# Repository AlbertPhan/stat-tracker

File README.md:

### For more pictures and info see:
www.pegasusprototyping.ca/stattracker

# Stat Tracker
The ***Stat Tracker*** is a portable battery powered device that keeps track of ***health, energy, and dashes*** for the Hyper Light Drifter Table Top Role Playing Game. Although it was designed with Hyper Light Drifter in mind, it could be used in other table top games like Dungeons and Dragons. 

Features:

 - Tracks 40 points of Health and Energy and 10 points in Dashes
 - Bright RGB leds for each icon
 - Custom art in Hyper Light Drifter theme
 - Unique Slim PCB sandwich construction with special icons for LED diffusion
 - 6 physical pcb buttons to add/subtract points
 - 2 touch buttons for brightness control
 - Customizable colour palettes including colourblind modes
 - USB micro for charging
 - 8 hours of battery life on default brightness and battery charge indicator icon
 - Stats are saved on power off.

 # Code

 The stat tracker uses a very cheap 50 cent chinese mcu called the CH552. The tool chain setup is explained in https://github.com/Blinkinlabs/ch554_sdcc.

 The stat tracker code is contained in the examples folder "examples/stat_tracker"

 Some c files were created/modified to help use the ch552 such as:
 - button.c     usage of buttons and their states
 - touch.c      touch button usage
 - timer.c      set up timers for millis()

 # Eagle Source files

Eagle Source files are included. (Eagle Version 9.6.1 was used). See README in Eagle files for bom/board information.

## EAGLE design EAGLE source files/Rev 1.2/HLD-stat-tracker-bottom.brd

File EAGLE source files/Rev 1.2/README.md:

# Boards
For a full PCB sandwich you will need:
1 Top
1 Middle
1 Bottom
3 Spacers
1 Box Art
Send additional info the board house such as led pinout png and note that the pads on the bottom of the bottom board are supposed to have solder mask (no exposed pad) over them.

# BOM
Bom is located in the GERBER bottom assembly "\Rev 1.2\Gerber\HLD-stat-tracker-bottom_2020-12-04\CAMOutputs\Assembly\HLD-stat-tracker-bottom-BOM.csv"
LEDS used are a 2020 type with SK6812 like pinout (not the same as ws2812-2020). Please triple check the pinouts if you are using something other than leds in the BOM.

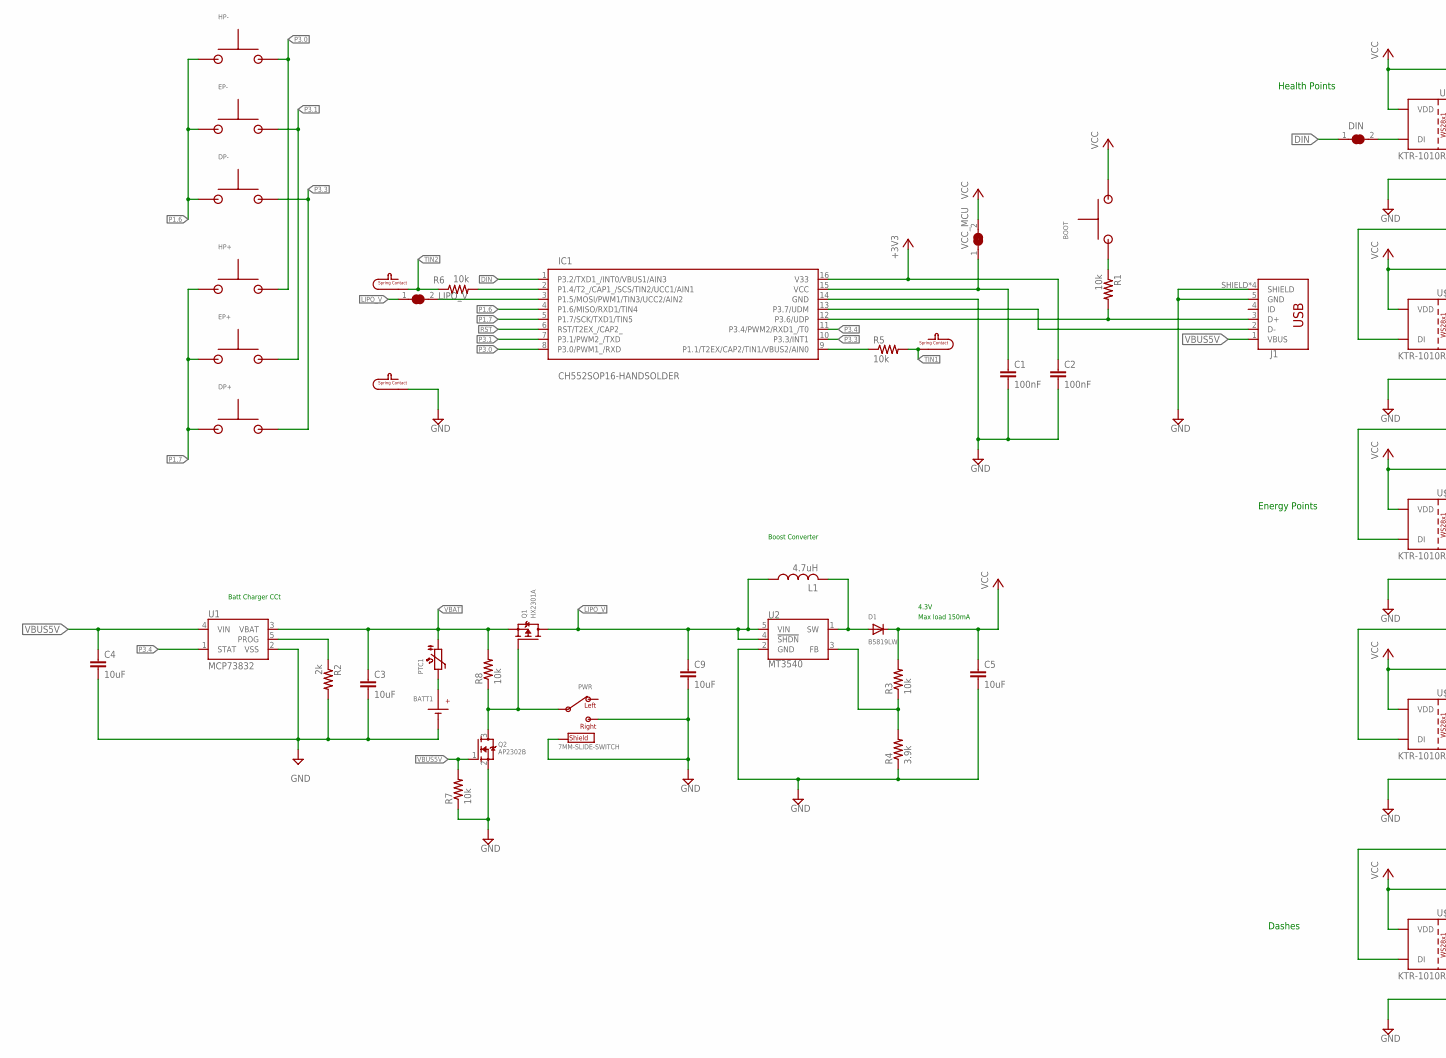
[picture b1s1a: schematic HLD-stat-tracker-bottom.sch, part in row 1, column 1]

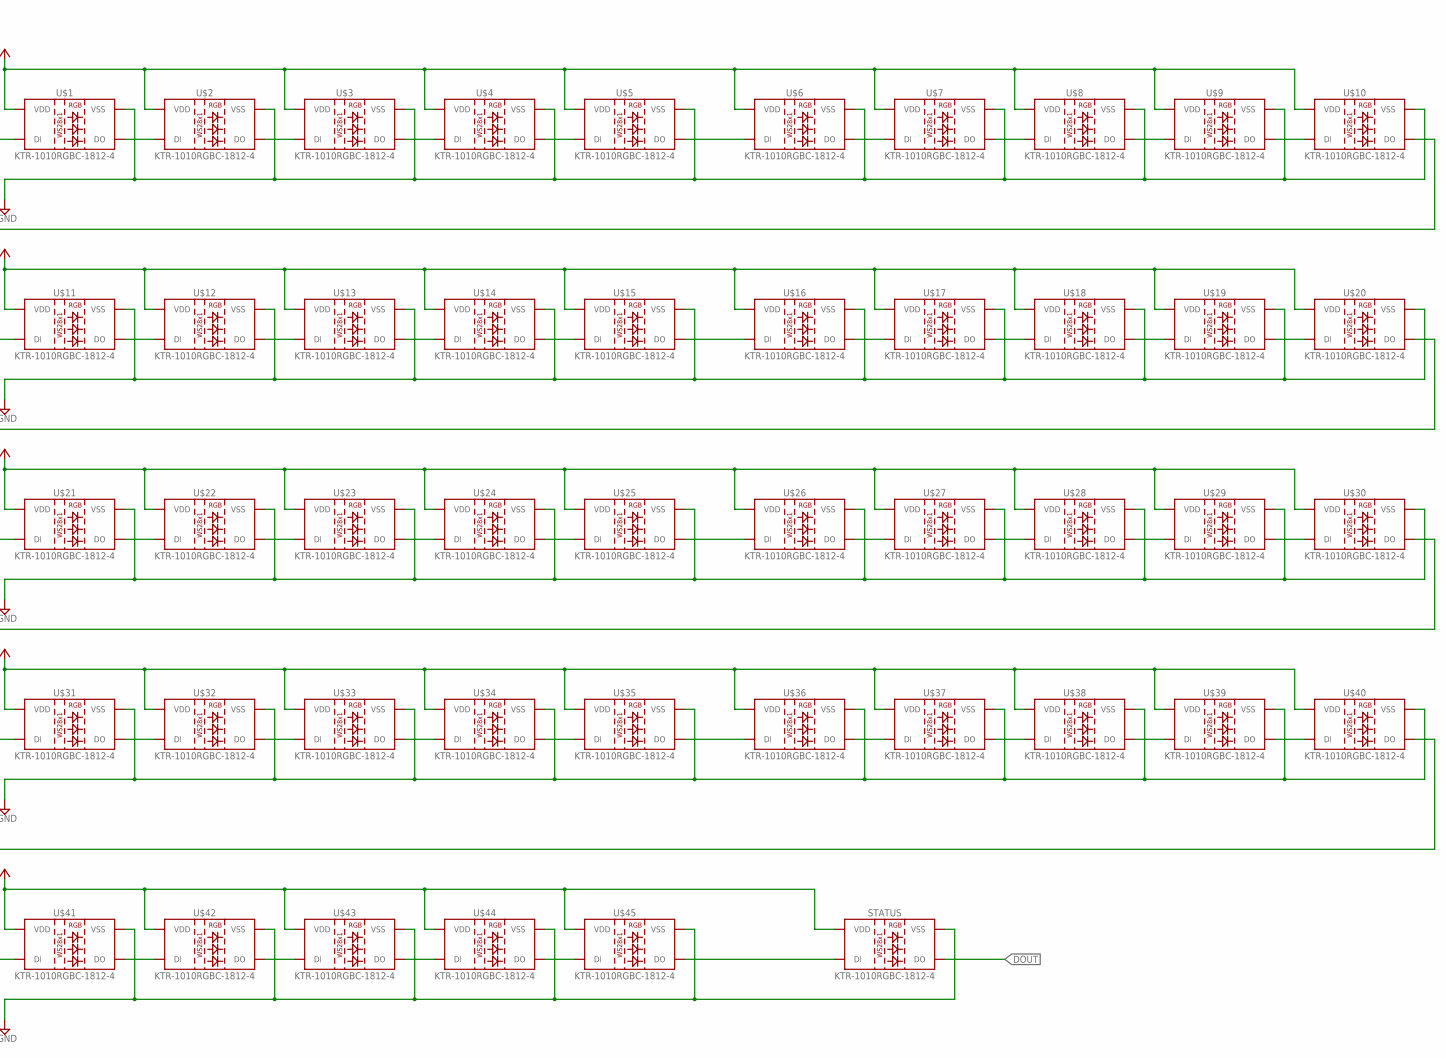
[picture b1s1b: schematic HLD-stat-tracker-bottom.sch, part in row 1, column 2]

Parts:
BATT1: BATT+; BATT+PAD; PARTNO ?
BATT1-: BATT-; BATT-PAD; PARTNO ?
BOOT: TACTSW; 3MM-TACT
C1, C2: 100nF; C0805K; PARTNO ?
C3, C4, C5, C9: 10uF; C0805K; PARTNO ?
D1: B5819LW; SOD-123; PARTNO B5819LW
DIN: SOLDERJUMPER-NC; SOLDERJUMPER_CLOSEDWIRE_SMALL
DP+: TACTSW; 3MM-TACT
DP-: TACTSW; 3MM-TACT
EP+: TACTSW; 3MM-TACT
EP-: TACTSW; 3MM-TACT
GND: SPRING-CONTACT; 818000905-SPRING-CONTACT
HP+: TACTSW; 3MM-TACT
HP-: TACTSW; 3MM-TACT; PARTNO TS3315A
IC1: CH552SOP16-HANDSOLDER; SOP16-HANDSOLDER
J1: USB_MICRO-BSINK-PLATE; USB-B-MICRO-SMD-SINK-PLATE
L1: 4.7uH; BEADC2012X105N
LIPO_V: SOLDERJUMPER-NC; SOLDERJUMPER_CLOSEDWIRE_SMALL
PTC1: PTC0805; WCAP-CSGP_0805_H1.25_R
PWR: 7MM-SLIDE-SWITCH; 7MM-SMD-SLIDE-SWITCH
Q1: HX2301A; SOT23-R
Q2: AP2302B; SOT23-R
R1, R3, R5, R6, R7, R8: 10k; R0805S; PARTNO ?
R2: 2k; R0805S; PARTNO ?
R4: 3.9k; R0805S; PARTNO ?
STATUS: KTR-1010RGBC-1812-4; SK6812-2020
TIN1, TIN2: SPRING-CONTACT; 818000905-SPRING-CONTACT
U1: MCP73832; SOT23-5; PARTNO MCP73832
U2: MT3540; SOT23-5; PARTNO MT3540
U$1, U$2, U$3, U$4, U$5, U$6, U$7, U$8, U$9, U$10, U$11, U$12, U$13, U$14, U$15, U$16, U$17, U$18, U$19, U$20, U$21, U$22, U$23, U$24, U$25, U$26, U$27, U$28, U$29, U$30, U$31, U$32, U$33, U$34, U$35, U$36, U$37, U$38, U$39, U$40, U$41, U$42, U$43, U$44, U$45: KTR-1010RGBC-1812-4; SK6812-2020
VCC_MCU: SOLDERJUMPER-NC; SOLDERJUMPER_CLOSEDWIRE_SMALL

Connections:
+3V3: C2.1, IC1.16 (V33)
DIN: DIN.1, IC1.1 (P3.2/TXD1_/INT0/VBUS1/AIN3)
DIN_: DIN.2, U$1.DIN (DI)
DOUT: STATUS.DOUT (DO)
FB: R3.1, R4.2, U2.3 (FB)
GND: BATT1-.P$1, C1.2, C2.2, C3.2, C4.2, C5.2, C9.2, GND.P$1, IC1.14 (GND), J1.5 (GND), J1.SHIELD, J1.SHIELD2 (SHIELD), J1.SHIELD3 (SHIELD), J1.SHIELD4 (SHIELD), PWR.3, PWR.GND@1 (SHIELD), PWR.GND@2 (SHIELD), PWR.GND@3 (SHIELD), PWR.GND@4 (SHIELD), Q2.2 (S), R2.2, R4.1, R7.1, STATUS.VSS, U1.2 (VSS), U2.2 (GND), U$1.VSS, U$2.VSS, U$3.VSS, U$4.VSS, U$5.VSS, U$6.VSS, U$7.VSS, U$8.VSS, U$9.VSS, U$10.VSS, U$11.VSS, U$12.VSS, U$13.VSS, U$14.VSS, U$15.VSS, U$16.VSS, U$17.VSS, U$18.VSS, U$19.VSS, U$20.VSS, U$21.VSS, U$22.VSS, U$23.VSS, U$24.VSS, U$25.VSS, U$26.VSS, U$27.VSS, U$28.VSS, U$29.VSS, U$30.VSS, U$31.VSS, U$32.VSS, U$33.VSS, U$34.VSS, U$35.VSS, U$36.VSS, U$37.VSS, U$38.VSS, U$39.VSS, U$40.VSS, U$41.VSS, U$42.VSS, U$43.VSS, U$44.VSS, U$45.VSS
LIPO_V: C9.1, L1.1, LIPO_V.1, Q1.3 (D), U2.4 (!SHDN!), U2.5 (VIN)
LIPO_V_MCU: IC1.3 (P1.5/MOSI/PWM1/TIN3/UCC2/AIN2), LIPO_V.2
unnamed: IC1.9 (P1.1/T2EX/CAP2/TIN1/VBUS2/AIN0), R5.1
unnamed: BATT1.P$1, PTC1.2
unnamed: IC1.2 (P1.4/T2_/CAP1_/SCS/TIN2/UCC1/AIN1), R6.2
unnamed: PWR.2, Q1.1 (G), Q2.3 (D), R8.1
unnamed: U$1.DOUT (DO), U$2.DIN (DI)
unnamed: U$6.DOUT (DO), U$7.DIN (DI)
unnamed: R2.1, U1.5 (PROG)
unnamed: U$20.DOUT (DO), U$21.DIN (DI)
unnamed: U$11.DOUT (DO), U$12.DIN (DI)
unnamed: U$16.DOUT (DO), U$17.DIN (DI)
unnamed: U$12.DOUT (DO), U$13.DIN (DI)
unnamed: U$13.DOUT (DO), U$14.DIN (DI)
unnamed: U$14.DOUT (DO), U$15.DIN (DI)
unnamed: U$15.DOUT (DO), U$16.DIN (DI)
unnamed: U$2.DOUT (DO), U$3.DIN (DI)
unnamed: U$3.DOUT (DO), U$4.DIN (DI)
unnamed: U$4.DOUT (DO), U$5.DIN (DI)
unnamed: U$5.DOUT (DO), U$6.DIN (DI)
unnamed: U$7.DOUT (DO), U$8.DIN (DI)
unnamed: U$8.DOUT (DO), U$9.DIN (DI)
unnamed: U$9.DOUT (DO), U$10.DIN (DI)
unnamed: U$17.DOUT (DO), U$18.DIN (DI)
unnamed: U$18.DOUT (DO), U$19.DIN (DI)
unnamed: U$19.DOUT (DO), U$20.DIN (DI)
unnamed: U$10.DOUT (DO), U$11.DIN (DI)
unnamed: U$21.DOUT (DO), U$22.DIN (DI)
unnamed: U$26.DOUT (DO), U$27.DIN (DI)
unnamed: U$22.DOUT (DO), U$23.DIN (DI)
unnamed: U$23.DOUT (DO), U$24.DIN (DI)
unnamed: U$24.DOUT (DO), U$25.DIN (DI)
unnamed: U$25.DOUT (DO), U$26.DIN (DI)
unnamed: U$27.DOUT (DO), U$28.DIN (DI)
unnamed: U$28.DOUT (DO), U$29.DIN (DI)
unnamed: U$29.DOUT (DO), U$30.DIN (DI)
unnamed: U$31.DOUT (DO), U$32.DIN (DI)
unnamed: U$36.DOUT (DO), U$37.DIN (DI)
unnamed: U$32.DOUT (DO), U$33.DIN (DI)
unnamed: U$33.DOUT (DO), U$34.DIN (DI)
unnamed: U$34.DOUT (DO), U$35.DIN (DI)
unnamed: U$35.DOUT (DO), U$36.DIN (DI)
unnamed: U$37.DOUT (DO), U$38.DIN (DI)
unnamed: U$38.DOUT (DO), U$39.DIN (DI)
unnamed: U$39.DOUT (DO), U$40.DIN (DI)
unnamed: U$30.DOUT (DO), U$31.DIN (DI)
unnamed: U$41.DOUT (DO), U$42.DIN (DI)
unnamed: U$42.DOUT (DO), U$43.DIN (DI)
unnamed: U$43.DOUT (DO), U$44.DIN (DI)
unnamed: U$44.DOUT (DO), U$45.DIN (DI)
unnamed: STATUS.DIN (DI), U$45.DOUT (DO)
unnamed: U$40.DOUT (DO), U$41.DIN (DI)
unnamed: BOOT.1, BOOT.2, R1.1
P1.6: DP-.1, DP-.2, EP-.1, EP-.2, HP-.1, HP-.2, IC1.4 (P1.6/MISO/RXD1/TIN4)
P1.7: DP+.1, DP+.2, EP+.1, EP+.2, HP+.1, HP+.2, IC1.5 (P1.7/SCK/TXD1/TIN5)
P3.0: HP+.3, HP+.4, HP-.3, HP-.4, IC1.8 (P3.0/PWM1_/RXD)
P3.1: EP+.3, EP+.4, EP-.3, EP-.4, IC1.7 (P3.1/PWM2_/TXD)
P3.3: DP+.3, DP+.4, DP-.3, DP-.4, IC1.10 (P3.3/INT1)
P3.4: IC1.11 (P3.4/PWM2/RXD1_/T0), U1.1 (STAT)
RST: IC1.6 (RST/T2EX_/CAP2_)
SW: D1.A, L1.2, U2.1 (SW)
TIN1: R5.2, TIN1.P$1
TIN2: R6.1, TIN2.P$1
UDM: IC1.13 (P3.7/UDM), J1.2 (D-)
UDP: IC1.12 (P3.6/UDP), J1.3 (D+), R1.2
VBAT: C3.1, PTC1.1, Q1.2 (S), R8.2, U1.3 (VBAT)
VBUS5V: C4.1, J1.1 (VBUS), Q2.1 (G), R7.2, U1.4 (VIN)
VCC: BOOT.3, BOOT.4, C5.1, D1.C, R3.2, STATUS.VDD, U$1.VDD, U$2.VDD, U$3.VDD, U$4.VDD, U$5.VDD, U$6.VDD, U$7.VDD, U$8.VDD, U$9.VDD, U$10.VDD, U$11.VDD, U$12.VDD, U$13.VDD, U$14.VDD, U$15.VDD, U$16.VDD, U$17.VDD, U$18.VDD, U$19.VDD, U$20.VDD, U$21.VDD, U$22.VDD, U$23.VDD, U$24.VDD, U$25.VDD, U$26.VDD, U$27.VDD, U$28.VDD, U$29.VDD, U$30.VDD, U$31.VDD, U$32.VDD, U$33.VDD, U$34.VDD, U$35.VDD, U$36.VDD, U$37.VDD, U$38.VDD, U$39.VDD, U$40.VDD, U$41.VDD, U$42.VDD, U$43.VDD, U$44.VDD, U$45.VDD, VCC_MCU.2
VCC_MCU: C1.1, IC1.15 (VCC), VCC_MCU.1

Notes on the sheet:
Health Points
Energy Points
Dashes
Batt Charger CCt
Boost Converter
Max load 150mA
4.3V

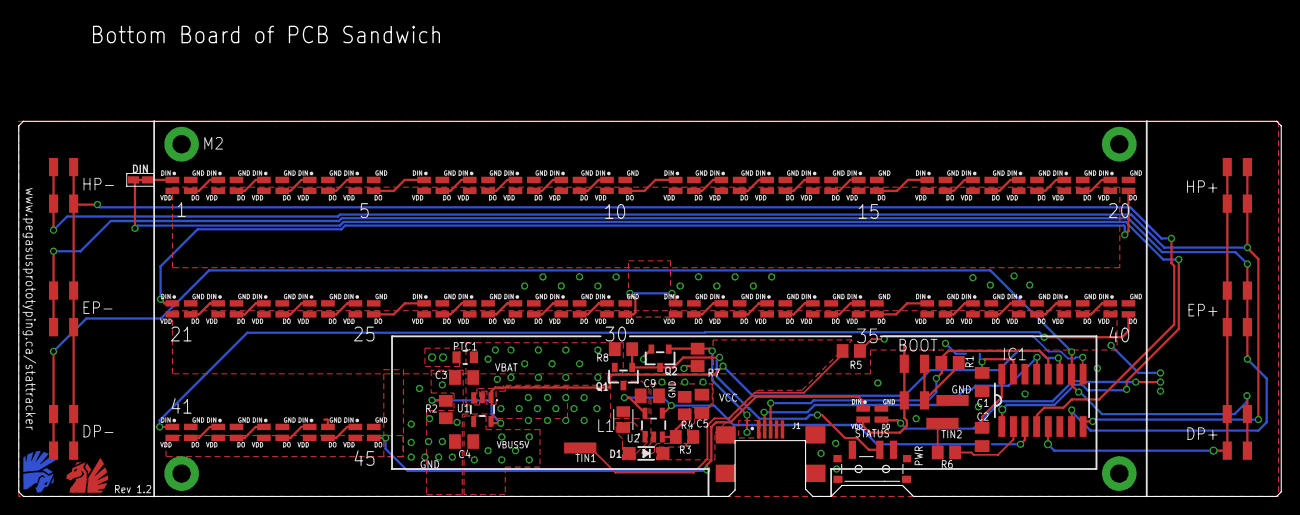
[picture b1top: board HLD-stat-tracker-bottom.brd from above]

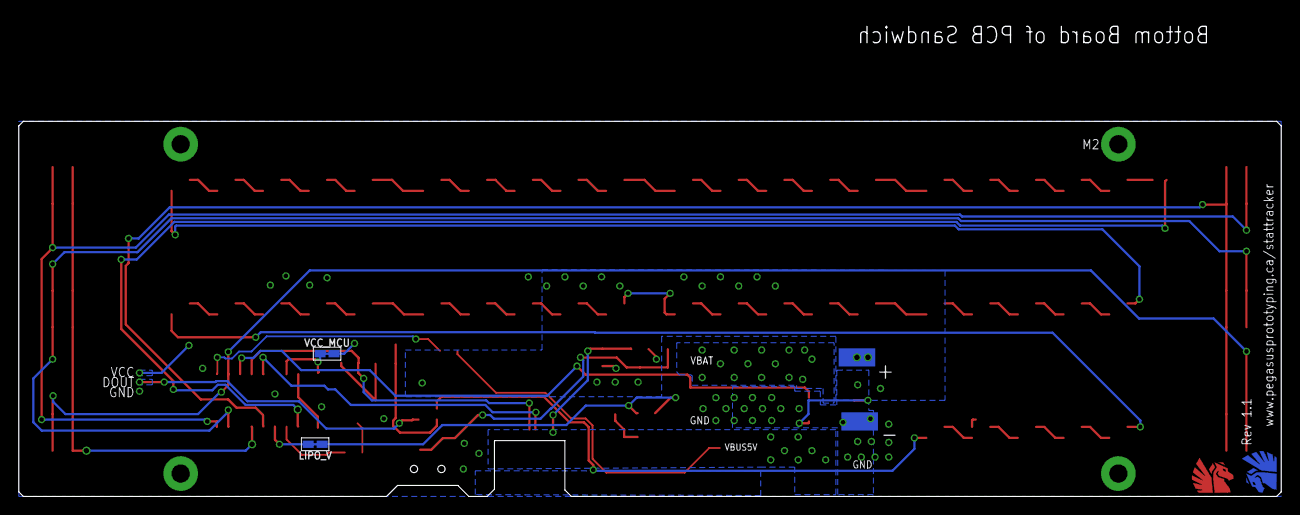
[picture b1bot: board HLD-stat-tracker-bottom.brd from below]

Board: 2 copper layers, 138.0 x 52.2 mm, 87 parts (5 on the bottom side), 73 nets.

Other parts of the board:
U$52, U$53: PEGASUSPROTOTYPING_5MM_COPPER

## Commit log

2020-03-31 Initial Commit
    Most LED and button Functionality complete.
2020-03-31 Adjusted main colours for health, energy and dashes
2020-04-02 Got touch key buttons working
    Added touch.c and touch.h. the chinese examples weren't working so I redid all the code.
    Started copying over some usb cdc files for the future
2020-04-04 Added millis() with timer0
    fixed map() function
    fixed battery color getting mapped twice incorrectly
    renamed colors to hsv for better tab completion
    added battery and timer debug states
    added set_battery_icon_led() for setting battery colours
    added clear_display()
2020-04-06 Fixed main loop timing issue and added USB for debugging
    Main loop would intermittenly break - causing the main loop to run as fast as it could. Adding an additional check for (prev_millis < current_millis) seemed to fix it. See line 554 in main.c
    USB stuff was added and can be enabled with a define for debugging.
2020-04-11 Lots of fixes and updates
    A lot of the charging status has been updated
    Major timing bug fixed ( thought to be fixed before but wasnt) - Timer ISR was happening during 4 byte copy of millis() causing errors.
    Added fade struct to help with fading batt icon
    Display dims when low batt
    Flashing on low batt
    Button states being worked on to implement retriggering
2020-04-13 Updated fully charged button icon behavior
2020-04-14 Added retrigger() to button functionality and separated it to button.c
    button debouncing added to button.c
    It uses lock-out interval style debouncing
2020-04-15 Fixed battery icon fading after constant voltage timeout.
    Define didn't seem to like (60*1000) so changed to single number i.e 60000 or 300000 for 3 minutes.
    Also fixed some include issues in button.c by adding ch554.h in the timer.h
2020-04-16 Added touchkey support
2020-04-17 Added a long_held state for tkey in button.c
    Changed up BUTTON state to debug the touchkeys instead of dash button.
2020-04-18 Changed to 16 bit for button timing to save space
    Don't need the extra 16 bits for button timing.
    Updated button debug state to show data on any button pressed
2020-04-19 Added a way to check if button state was long held and deactivated
2020-04-19 Started added "EEPROM" code for remembering colour config
2020-04-20 Changed how retrigger() works
    retrigger now does not activate on first press.
    Now we can use long_held() without activating the button on the initial press. This is useful for going into configuration states.
2020-04-22 Added colour palettes and some default colours.
2020-04-24 Some colour config done.
    In the config state, the custom colour palette can be edited
2020-04-29 Added colour configuration and saving.
    Also fixed max codesize to be correctly 14KiB for the CH552
2020-04-30 Added colour configuration and saving
    forgot to commit the main.c file
2020-04-30 Stats are now saved to eeprom
2020-07-21 Rev 1.0 Board working
    Updated touch code for new board.
    Added charging status screen when charging
    Adjusted ADC values for new 4.28 VCC
    Fixed Battery led bars showing incorrect voltage/charge state
    Adjusted min brightness values during fading to stop hue changes
    Adjusted bitbang timing for ws2812 leds to fix flickering leds. (May require more testing)
2020-07-22 Brightness is now saved between resets
2020-09-28 Changed how fade animating works
    fading now works by grabbing the correct fading frame to be displayed
    while an update fade function updates the animation once per loop.
    ws2812 example bitbanging was adjusted to provide correct timing for the
    ws2812-2020 version of the led
2021-02-12 Addressable LED bitbang library cleaned up
    -Changed how Bitbang library is used to facilitate multiple types of
    leds. See bitbang.c in the include folder for details.
    -Added a startup animation to the stat tracker
    -Fixed Main loop not running at LOOP_PERIOD_MS intervals.
    -
2021-02-18 Updated Readme. Added Eagle source files.

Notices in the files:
parts and their libraries:
SparkFun-PowerIC: Licensing: Creative Commons ShareAlike 4.0 International - https://creativecommons.org/licenses/by-sa/4.0
microbuilder: This work is placed in the public domain, and may be freely used for commercial and non-commercial work with the following conditions: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
